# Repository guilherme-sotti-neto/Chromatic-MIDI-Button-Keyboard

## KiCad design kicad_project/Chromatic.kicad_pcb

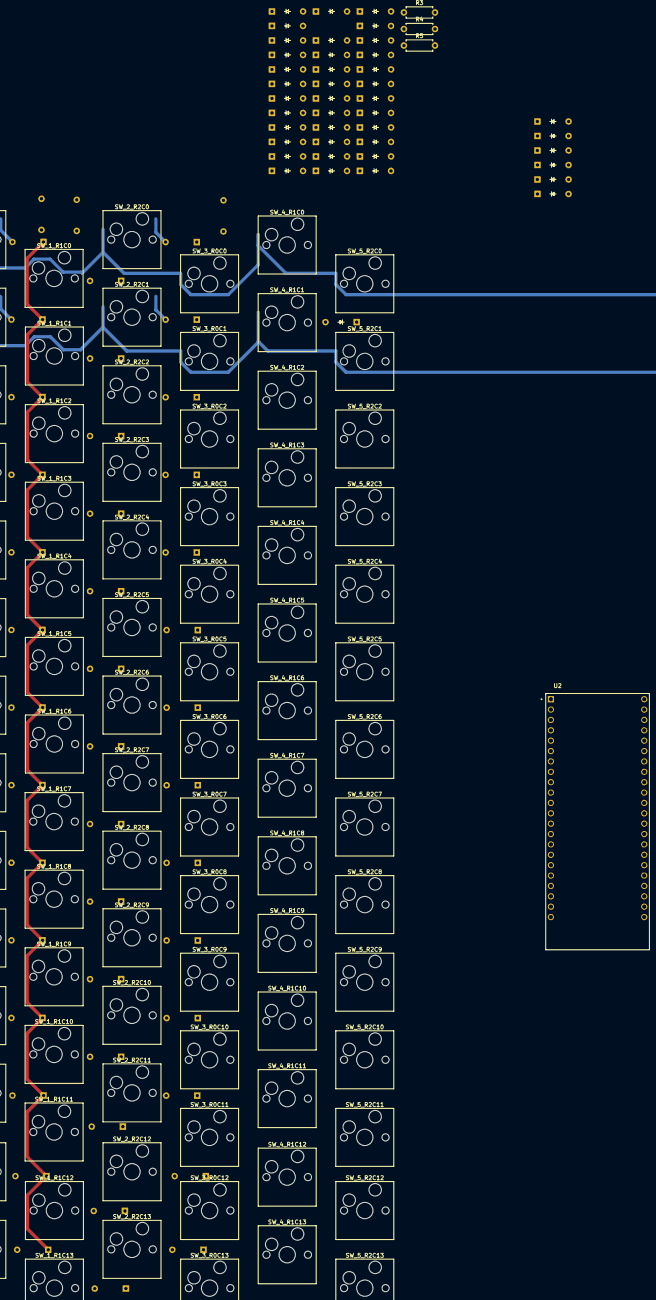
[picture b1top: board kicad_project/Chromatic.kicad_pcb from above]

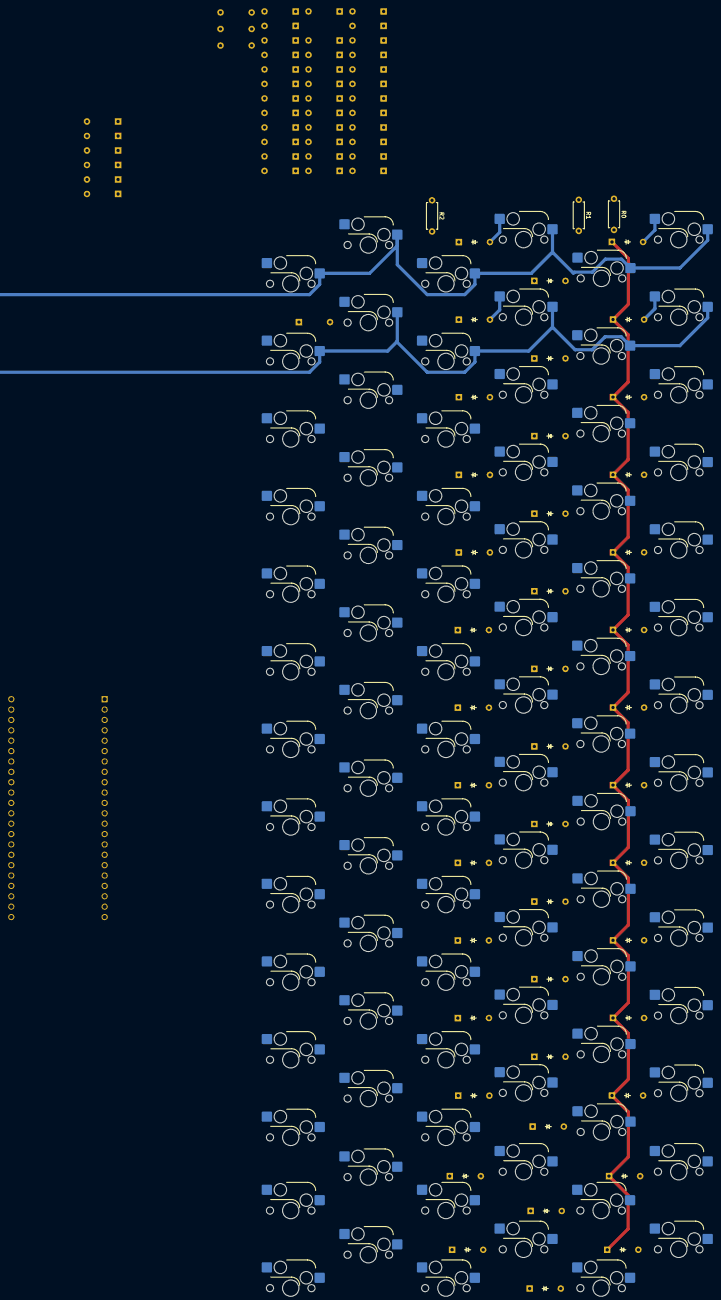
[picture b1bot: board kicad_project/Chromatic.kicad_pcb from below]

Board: 2 copper layers, 175 parts (45 on the bottom side), 108 nets.

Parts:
D_R0C0, D_R0C1, D_R0C2, D_R0C3, D_R0C4, D_R0C5, D_R0C6, D_R0C7, D_R0C8, D_R0C9, D_R0C10, D_R0C11, D_R0C12, D_R0C13, D_R1C0, D_R1C1, D_R1C2, D_R1C3, D_R1C4, D_R1C5, D_R1C6, D_R1C7, D_R1C8, D_R1C9, D_R1C10, D_R1C11, D_R1C12, D_R1C13, D_R2C0, D_R2C1, D_R2C2, D_R2C3, D_R2C4, D_R2C5, D_R2C6, D_R2C7, D_R2C8, D_R2C9, D_R2C10, D_R2C11, D_R2C12, D_R2C13, D_R2C17, D_R2C18, D_R2C19, D_R2C20, D_R2C21, D_R2C22, D_R2C23, D_R2C24, D_R2C25, D_R2C26, D_R2C27, D_R2C28, D_R2C29, D_R2C30, D_R2C31, D_R2C32, D_R2C33, D_R2C34, D_R2C35, D_R2C36, D_R2C37, D_R2C38, D_R2C39, D_R2C40, D_R2C41, D_R2C42, D_R2C43, D_R2C44, D_R2C45, D_R2C46, D_R2C47, D_R2C48, D_R2C49, D_R2C50, D_R2C51, D_R2C52, D_R2C53, D_R2C54, D_R2C55, D_R2C56, D_R2C57, D_R2C58: Diode_DO-35
R0, R1, R2, R3, R4, R5: Resistor; R_Axial_DIN0207_L6.3mm_D2.5mm_P7.62mm_Horizontal
SW_0_R0C0, SW_0_R0C1, SW_0_R0C2, SW_0_R0C3, SW_0_R0C4, SW_0_R0C5, SW_0_R0C6, SW_0_R0C7, SW_0_R0C8, SW_0_R0C9, SW_0_R0C10, SW_0_R0C11, SW_0_R0C12, SW_0_R0C13, SW_1_R1C0, SW_1_R1C1, SW_1_R1C2, SW_1_R1C3, SW_1_R1C4, SW_1_R1C5, SW_1_R1C6, SW_1_R1C7, SW_1_R1C8, SW_1_R1C9, SW_1_R1C10, SW_1_R1C11, SW_1_R1C12, SW_1_R1C13, SW_2_R2C0, SW_2_R2C1, SW_2_R2C2, SW_2_R2C3, SW_2_R2C4, SW_2_R2C5, SW_2_R2C6, SW_2_R2C7, SW_2_R2C8, SW_2_R2C9, SW_2_R2C10, SW_2_R2C11, SW_2_R2C12, SW_2_R2C13, SW_3_R0C0, SW_3_R0C1, SW_3_R0C2, SW_3_R0C3, SW_3_R0C4, SW_3_R0C5, SW_3_R0C6, SW_3_R0C7, SW_3_R0C8, SW_3_R0C9, SW_3_R0C10, SW_3_R0C11, SW_3_R0C12, SW_3_R0C13, SW_4_R1C0, SW_4_R1C1, SW_4_R1C2, SW_4_R1C3, SW_4_R1C4, SW_4_R1C5, SW_4_R1C6, SW_4_R1C7, SW_4_R1C8, SW_4_R1C9, SW_4_R1C10, SW_4_R1C11, SW_4_R1C12, SW_4_R1C13, SW_5_R2C0, SW_5_R2C1, SW_5_R2C2, SW_5_R2C3, SW_5_R2C4, SW_5_R2C5, SW_5_R2C6, SW_5_R2C7, SW_5_R2C8, SW_5_R2C9, SW_5_R2C10, SW_5_R2C11, SW_5_R2C12, SW_5_R2C13: Keyswitch; Hotswap_MX_1.00u
U2: ESP32-S3-DEVKITC-1-N8R8

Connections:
Column 0: SW_0_R0C0.1, SW_1_R1C0.1, SW_2_R2C0.1, SW_3_R0C0.1, SW_4_R1C0.1, SW_5_R2C0.1, U2.J1_4 (GPIO4)
Column 1: SW_0_R0C1.1, SW_1_R1C1.1, SW_2_R2C1.1, SW_3_R0C1.1, SW_4_R1C1.1, SW_5_R2C1.1, U2.J1_5 (GPIO5)
Column 2: SW_0_R0C2.1, SW_1_R1C2.1, SW_2_R2C2.1, SW_3_R0C2.1, SW_4_R1C2.1, SW_5_R2C2.1, U2.J1_6 (GPIO6)
Column 3: SW_0_R0C3.1, SW_1_R1C3.1, SW_2_R2C3.1, SW_3_R0C3.1, SW_4_R1C3.1, SW_5_R2C3.1, U2.J1_7 (GPIO7)
Column 4: SW_0_R0C4.1, SW_1_R1C4.1, SW_2_R2C4.1, SW_3_R0C4.1, SW_4_R1C4.1, SW_5_R2C4.1, U2.J1_8 (GPIO15)
Column 5: SW_0_R0C5.1, SW_1_R1C5.1, SW_2_R2C5.1, SW_3_R0C5.1, SW_4_R1C5.1, SW_5_R2C5.1, U2.J1_9 (GPIO16)
Column 6: SW_0_R0C6.1, SW_1_R1C6.1, SW_2_R2C6.1, SW_3_R0C6.1, SW_4_R1C6.1, SW_5_R2C6.1, U2.J1_10 (GPIO17)
Column 7: SW_0_R0C7.1, SW_1_R1C7.1, SW_2_R2C7.1, SW_3_R0C7.1, SW_4_R1C7.1, SW_5_R2C7.1, U2.J1_11 (GPIO18)
Column 8: SW_0_R0C8.1, SW_1_R1C8.1, SW_2_R2C8.1, SW_3_R0C8.1, SW_4_R1C8.1, SW_5_R2C8.1, U2.J1_12 (GPIO8)
Column 9: SW_0_R0C9.1, SW_0_R0C12.1, SW_1_R1C9.1, SW_1_R1C12.1, SW_2_R2C9.1, SW_2_R2C12.1, SW_3_R0C9.1, SW_3_R0C12.1, SW_4_R1C9.1, SW_4_R1C12.1, SW_5_R2C9.1, SW_5_R2C12.1, U2.J1_13 (GPIO3)
Column 10: SW_0_R0C10.1, SW_0_R0C13.1, SW_1_R1C10.1, SW_1_R1C13.1, SW_2_R2C10.1, SW_2_R2C13.1, SW_3_R0C10.1, SW_3_R0C13.1, SW_4_R1C10.1, SW_4_R1C13.1, SW_5_R2C10.1, SW_5_R2C13.1, U2.J1_14 (GPIO46)
Column 11: SW_0_R0C11.1, SW_1_R1C11.1, SW_2_R2C11.1, SW_3_R0C11.1, SW_4_R1C11.1, SW_5_R2C11.1, U2.J1_15 (GPIO9)
unnamed: D_R0C0.2 (A), SW_0_R0C0.2
unnamed: D_R0C0.1 (K), D_R0C1.1 (K), D_R0C2.1 (K), D_R0C3.1 (K), D_R0C4.1 (K), D_R0C5.1 (K), D_R0C6.1 (K), D_R0C7.1 (K), D_R0C8.1 (K), D_R0C9.1 (K), D_R0C10.1 (K), D_R0C11.1 (K), D_R0C12.1 (K), D_R0C13.1 (K), R0.2
unnamed: D_R0C1.2 (A), SW_0_R0C1.2
unnamed: D_R0C2.2 (A), SW_0_R0C2.2
unnamed: D_R0C3.2 (A), SW_0_R0C3.2
unnamed: D_R0C4.2 (A), SW_0_R0C4.2
unnamed: D_R0C5.2 (A), SW_0_R0C5.2
unnamed: D_R0C6.2 (A), SW_0_R0C6.2
unnamed: D_R0C7.2 (A), SW_0_R0C7.2
unnamed: D_R0C8.2 (A), SW_0_R0C8.2
unnamed: D_R0C9.2 (A), SW_0_R0C9.2
unnamed: D_R0C10.2 (A), SW_0_R0C10.2
unnamed: D_R0C11.2 (A), SW_0_R0C11.2
unnamed: D_R0C12.2 (A), SW_0_R0C12.2
unnamed: D_R0C13.2 (A), SW_0_R0C13.2
unnamed: D_R1C0.2 (A), SW_1_R1C0.2
unnamed: D_R1C0.1 (K), D_R1C1.1 (K), D_R1C2.1 (K), D_R1C3.1 (K), D_R1C4.1 (K), D_R1C5.1 (K), D_R1C6.1 (K), D_R1C7.1 (K), D_R1C8.1 (K), D_R1C9.1 (K), D_R1C10.1 (K), D_R1C11.1 (K), D_R1C12.1 (K), D_R1C13.1 (K), R1.2
unnamed: D_R1C1.2 (A), SW_1_R1C1.2
unnamed: D_R1C2.2 (A), SW_1_R1C2.2
unnamed: D_R1C3.2 (A), SW_1_R1C3.2
unnamed: D_R1C4.2 (A), SW_1_R1C4.2
unnamed: D_R1C5.2 (A), SW_1_R1C5.2
unnamed: D_R1C6.2 (A), SW_1_R1C6.2
unnamed: D_R1C7.2 (A), SW_1_R1C7.2
unnamed: D_R1C8.2 (A), SW_1_R1C8.2
unnamed: D_R1C9.2 (A), SW_1_R1C9.2
unnamed: D_R1C10.2 (A), SW_1_R1C10.2
unnamed: D_R1C11.2 (A), SW_1_R1C11.2
unnamed: D_R1C12.2 (A), SW_1_R1C12.2
unnamed: D_R1C13.2 (A), SW_1_R1C13.2
unnamed: D_R2C0.2 (A), SW_2_R2C0.2
unnamed: D_R2C0.1 (K), D_R2C1.1 (K), D_R2C2.1 (K), D_R2C3.1 (K), D_R2C4.1 (K), D_R2C5.1 (K), D_R2C6.1 (K), D_R2C7.1 (K), D_R2C8.1 (K), D_R2C9.1 (K), D_R2C10.1 (K), D_R2C11.1 (K), D_R2C12.1 (K), D_R2C13.1 (K), R2.2
unnamed: D_R2C1.2 (A), SW_2_R2C1.2
unnamed: D_R2C2.2 (A), SW_2_R2C2.2
unnamed: D_R2C3.2 (A), SW_2_R2C3.2
unnamed: D_R2C4.2 (A), SW_2_R2C4.2
unnamed: D_R2C5.2 (A), SW_2_R2C5.2
unnamed: D_R2C6.2 (A), SW_2_R2C6.2
unnamed: D_R2C7.2 (A), SW_2_R2C7.2
unnamed: D_R2C8.2 (A), SW_2_R2C8.2
unnamed: D_R2C9.2 (A), SW_2_R2C9.2
unnamed: D_R2C10.2 (A), SW_2_R2C10.2
unnamed: D_R2C11.2 (A), SW_2_R2C11.2
unnamed: D_R2C12.2 (A), SW_2_R2C12.2
unnamed: D_R2C13.2 (A), SW_2_R2C13.2
unnamed: D_R2C17.2 (A), SW_5_R2C0.2
unnamed: D_R2C17.1 (K), D_R2C18.1 (K), D_R2C19.1 (K), D_R2C20.1 (K), D_R2C21.1 (K), D_R2C22.1 (K), D_R2C23.1 (K), D_R2C24.1 (K), D_R2C25.1 (K), D_R2C26.1 (K), D_R2C27.1 (K), D_R2C28.1 (K), D_R2C55.1 (K), D_R2C58.1 (K), R3.2
unnamed: D_R2C18.2 (A), SW_5_R2C1.2
unnamed: D_R2C19.2 (A), SW_5_R2C2.2
unnamed: D_R2C20.2 (A), SW_5_R2C3.2
unnamed: D_R2C21.2 (A), SW_5_R2C4.2
unnamed: D_R2C22.2 (A), SW_5_R2C5.2
unnamed: D_R2C23.2 (A), SW_5_R2C6.2
unnamed: D_R2C24.2 (A), SW_5_R2C7.2
unnamed: D_R2C25.2 (A), SW_5_R2C8.2
unnamed: D_R2C26.2 (A), SW_5_R2C9.2
unnamed: D_R2C27.2 (A), SW_5_R2C10.2
unnamed: D_R2C28.2 (A), SW_5_R2C11.2
unnamed: D_R2C29.2 (A), SW_4_R1C0.2
unnamed: D_R2C29.1 (K), D_R2C30.1 (K), D_R2C31.1 (K), D_R2C32.1 (K), D_R2C33.1 (K), D_R2C34.1 (K), D_R2C35.1 (K), D_R2C36.1 (K), D_R2C37.1 (K), D_R2C38.1 (K), D_R2C39.1 (K), D_R2C40.1 (K), D_R2C54.1 (K), D_R2C57.1 (K), R4.2
unnamed: D_R2C30.2 (A), SW_4_R1C1.2
unnamed: D_R2C31.2 (A), SW_4_R1C2.2
unnamed: D_R2C32.2 (A), SW_4_R1C3.2
unnamed: D_R2C33.2 (A), SW_4_R1C4.2
unnamed: D_R2C34.2 (A), SW_4_R1C5.2
unnamed: D_R2C35.2 (A), SW_4_R1C6.2
unnamed: D_R2C36.2 (A), SW_4_R1C7.2
unnamed: D_R2C37.2 (A), SW_4_R1C8.2
unnamed: D_R2C38.2 (A), SW_4_R1C9.2
unnamed: D_R2C39.2 (A), SW_4_R1C10.2
unnamed: D_R2C40.2 (A), SW_4_R1C11.2
unnamed: D_R2C41.2 (A), SW_3_R0C0.2
unnamed: D_R2C41.1 (K), D_R2C42.1 (K), D_R2C43.1 (K), D_R2C44.1 (K), D_R2C45.1 (K), D_R2C46.1 (K), D_R2C47.1 (K), D_R2C48.1 (K), D_R2C49.1 (K), D_R2C50.1 (K), D_R2C51.1 (K), D_R2C52.1 (K), D_R2C53.1 (K), D_R2C56.1 (K), R5.2
unnamed: D_R2C42.2 (A), SW_3_R0C1.2
unnamed: D_R2C43.2 (A), SW_3_R0C2.2
unnamed: D_R2C44.2 (A), SW_3_R0C3.2
unnamed: D_R2C45.2 (A), SW_3_R0C4.2
unnamed: D_R2C46.2 (A), SW_3_R0C5.2
unnamed: D_R2C47.2 (A), SW_3_R0C6.2
unnamed: D_R2C48.2 (A), SW_3_R0C7.2
unnamed: D_R2C49.2 (A), SW_3_R0C8.2
unnamed: D_R2C50.2 (A), SW_3_R0C9.2
unnamed: D_R2C51.2 (A), SW_3_R0C10.2
unnamed: D_R2C52.2 (A), SW_3_R0C11.2
unnamed: D_R2C53.2 (A), SW_3_R0C12.2
unnamed: D_R2C54.2 (A), SW_4_R1C12.2
unnamed: D_R2C55.2 (A), SW_5_R2C12.2
unnamed: D_R2C56.2 (A), SW_3_R0C13.2
unnamed: D_R2C57.2 (A), SW_4_R1C13.2
unnamed: D_R2C58.2 (A), SW_5_R2C13.2
Row 0: R0.1, U2.J3_3 (U0RXD/GPIO44)
Row 1: R5.1, U2.J3_4 (GPIO1)
Row 2: R1.1, U2.J3_5 (GPIO2)
Row 3: R4.1, U2.J3_16 (GPIO48)
Row 4: R2.1, U2.J3_17 (GPIO47)
Row 5: R3.1, U2.J3_18 (GPIO21)

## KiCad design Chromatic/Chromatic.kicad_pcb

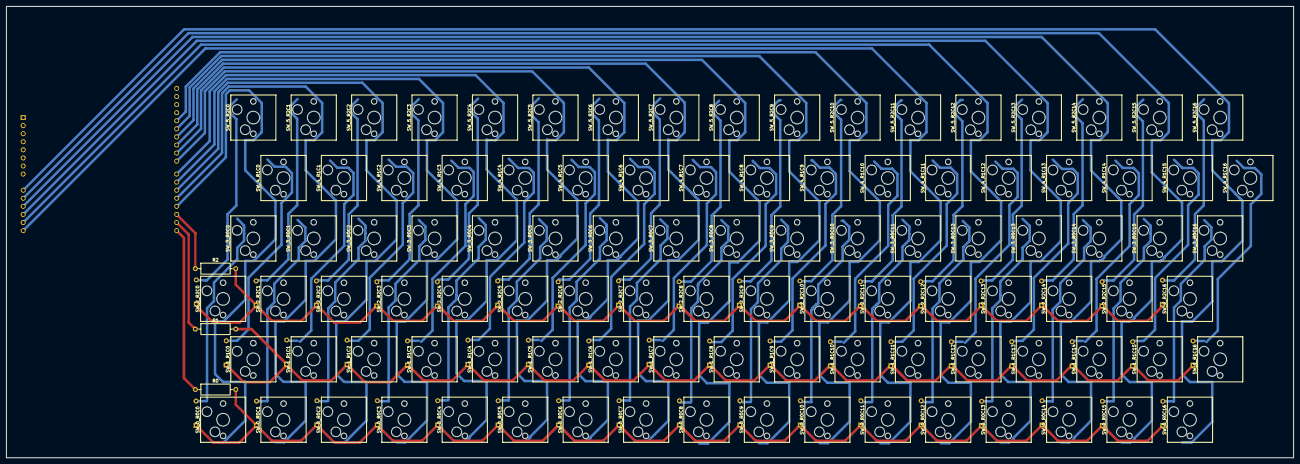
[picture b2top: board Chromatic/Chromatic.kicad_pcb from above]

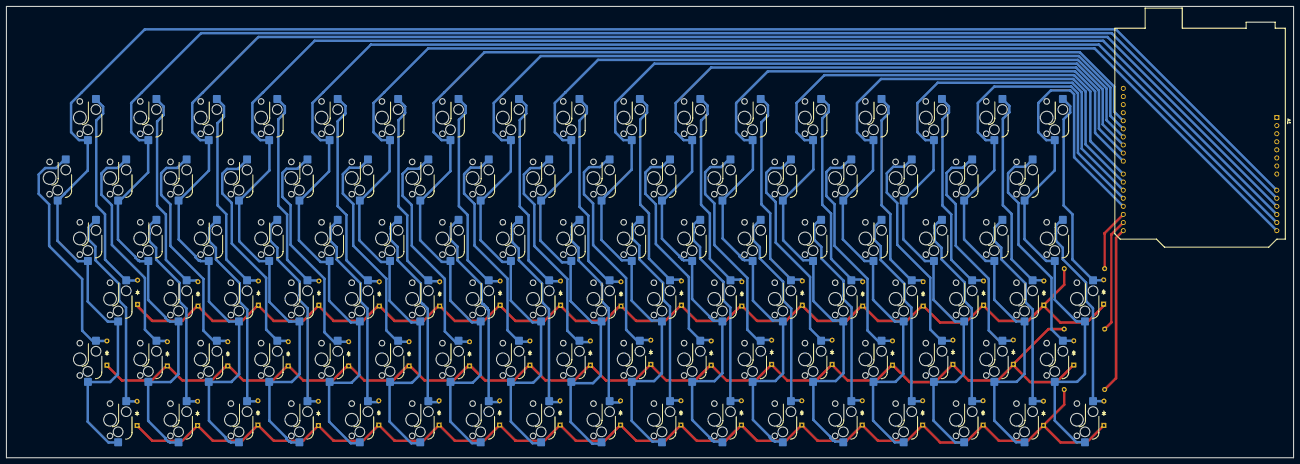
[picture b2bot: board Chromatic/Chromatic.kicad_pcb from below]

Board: 2 copper layers, 404.7 x 141.9 mm, 157 parts (52 on the bottom side), 74 nets.

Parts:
A1: Arduino_Leonardo; Arduino_UNO_R3
D_R0C0, D_R0C1, D_R0C2, D_R0C3, D_R0C4, D_R0C5, D_R0C6, D_R0C7, D_R0C8, D_R0C9, D_R0C10, D_R0C11, D_R0C12, D_R0C13, D_R0C14, D_R0C15, D_R0C16, D_R1C0, D_R1C1, D_R1C2, D_R1C3, D_R1C4, D_R1C5, D_R1C6, D_R1C7, D_R1C8, D_R1C9, D_R1C10, D_R1C11, D_R1C12, D_R1C13, D_R1C14, D_R1C15, D_R1C16, D_R2C0, D_R2C1, D_R2C2, D_R2C3, D_R2C4, D_R2C5, D_R2C6, D_R2C7, D_R2C8, D_R2C9, D_R2C10, D_R2C11, D_R2C12, D_R2C13, D_R2C14, D_R2C15, D_R2C16: Diode_DO-35
R0, R1, R2: Resistor; R_Axial_DIN0309_L9.0mm_D3.2mm_P12.70mm_Horizontal
SW_0_R0C0, SW_0_R0C1, SW_0_R0C2, SW_0_R0C3, SW_0_R0C4, SW_0_R0C5, SW_0_R0C6, SW_0_R0C7, SW_0_R0C8, SW_0_R0C9, SW_0_R0C10, SW_0_R0C11, SW_0_R0C12, SW_0_R0C13, SW_0_R0C14, SW_0_R0C15, SW_0_R0C16, SW_1_R1C0, SW_1_R1C1, SW_1_R1C2, SW_1_R1C3, SW_1_R1C4, SW_1_R1C5, SW_1_R1C6, SW_1_R1C7, SW_1_R1C8, SW_1_R1C9, SW_1_R1C10, SW_1_R1C11, SW_1_R1C12, SW_1_R1C13, SW_1_R1C14, SW_1_R1C15, SW_1_R1C16, SW_2_R2C0, SW_2_R2C1, SW_2_R2C2, SW_2_R2C3, SW_2_R2C4, SW_2_R2C5, SW_2_R2C6, SW_2_R2C7, SW_2_R2C8, SW_2_R2C9, SW_2_R2C10, SW_2_R2C11, SW_2_R2C12, SW_2_R2C13, SW_2_R2C14, SW_2_R2C15, SW_2_R2C16, SW_3_R0C0, SW_3_R0C1, SW_3_R0C2, SW_3_R0C3, SW_3_R0C4, SW_3_R0C5, SW_3_R0C6, SW_3_R0C7, SW_3_R0C8, SW_3_R0C9, SW_3_R0C10, SW_3_R0C11, SW_3_R0C12, SW_3_R0C13, SW_3_R0C14, SW_3_R0C15, SW_3_R0C16, SW_4_R1C0, SW_4_R1C1, SW_4_R1C2, SW_4_R1C3, SW_4_R1C4, SW_4_R1C5, SW_4_R1C6, SW_4_R1C7, SW_4_R1C8, SW_4_R1C9, SW_4_R1C10, SW_4_R1C11, SW_4_R1C12, SW_4_R1C13, SW_4_R1C14, SW_4_R1C15, SW_4_R1C16, SW_5_R2C0, SW_5_R2C1, SW_5_R2C2, SW_5_R2C3, SW_5_R2C4, SW_5_R2C5, SW_5_R2C6, SW_5_R2C7, SW_5_R2C8, SW_5_R2C9, SW_5_R2C10, SW_5_R2C11, SW_5_R2C12, SW_5_R2C13, SW_5_R2C14, SW_5_R2C15, SW_5_R2C16: Keyswitch; Hotswap_MX_1.00u

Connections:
Column 0: A1.18 (D3/SCL), SW_0_R0C0.1, SW_1_R1C0.1, SW_2_R2C0.1, SW_3_R0C0.1, SW_4_R1C0.1, SW_5_R2C0.1
Column 1: A1.19 (D4), SW_0_R0C1.1, SW_1_R1C1.1, SW_2_R2C1.1, SW_3_R0C1.1, SW_4_R1C1.1, SW_5_R2C1.1
Column 2: A1.20 (D5), SW_0_R0C2.1, SW_1_R1C2.1, SW_2_R2C2.1, SW_3_R0C2.1, SW_4_R1C2.1, SW_5_R2C2.1
Column 3: A1.21 (D6), SW_0_R0C3.1, SW_1_R1C3.1, SW_2_R2C3.1, SW_3_R0C3.1, SW_4_R1C3.1, SW_5_R2C3.1
Column 4: A1.22 (D7), SW_0_R0C4.1, SW_1_R1C4.1, SW_2_R2C4.1, SW_3_R0C4.1, SW_4_R1C4.1, SW_5_R2C4.1
Column 5: A1.23 (D8), SW_0_R0C5.1, SW_1_R1C5.1, SW_2_R2C5.1, SW_3_R0C5.1, SW_4_R1C5.1, SW_5_R2C5.1
Column 6: A1.24 (D9), SW_0_R0C6.1, SW_1_R1C6.1, SW_2_R2C6.1, SW_3_R0C6.1, SW_4_R1C6.1, SW_5_R2C6.1
Column 7: A1.25 (D10), SW_0_R0C7.1, SW_1_R1C7.1, SW_2_R2C7.1, SW_3_R0C7.1, SW_4_R1C7.1, SW_5_R2C7.1
Column 8: A1.26 (D11), SW_0_R0C8.1, SW_1_R1C8.1, SW_2_R2C8.1, SW_3_R0C8.1, SW_4_R1C8.1, SW_5_R2C8.1
Column 9: A1.27 (D12), SW_0_R0C9.1, SW_1_R1C9.1, SW_2_R2C9.1, SW_3_R0C9.1, SW_4_R1C9.1, SW_5_R2C9.1
Column 10: A1.28 (D13), SW_0_R0C10.1, SW_1_R1C10.1, SW_2_R2C10.1, SW_3_R0C10.1, SW_4_R1C10.1, SW_5_R2C10.1
Column 11: A1.14 (A5), SW_0_R0C11.1, SW_1_R1C11.1, SW_2_R2C11.1, SW_3_R0C11.1, SW_4_R1C11.1, SW_5_R2C11.1
Column 12: A1.13 (A4), SW_0_R0C12.1, SW_1_R1C12.1, SW_2_R2C12.1, SW_3_R0C12.1, SW_4_R1C12.1, SW_5_R2C12.1
Column 13: A1.12 (A3), SW_0_R0C13.1, SW_1_R1C13.1, SW_2_R2C13.1, SW_3_R0C13.1, SW_4_R1C13.1, SW_5_R2C13.1
Column 14: A1.11 (A2), SW_0_R0C14.1, SW_1_R1C14.1, SW_2_R2C14.1, SW_3_R0C14.1, SW_4_R1C14.1, SW_5_R2C14.1
Column 15: A1.10 (A1), SW_0_R0C15.1, SW_1_R1C15.1, SW_2_R2C15.1, SW_3_R0C15.1, SW_4_R1C15.1, SW_5_R2C15.1
Column 16: A1.9 (A0), SW_0_R0C16.1, SW_1_R1C16.1, SW_2_R2C16.1, SW_3_R0C16.1, SW_4_R1C16.1, SW_5_R2C16.1
unnamed: D_R0C0.2 (A), SW_0_R0C0.2, SW_3_R0C0.2
unnamed: D_R0C0.1 (K), D_R0C1.1 (K), D_R0C2.1 (K), D_R0C3.1 (K), D_R0C4.1 (K), D_R0C5.1 (K), D_R0C6.1 (K), D_R0C7.1 (K), D_R0C8.1 (K), D_R0C9.1 (K), D_R0C10.1 (K), D_R0C11.1 (K), D_R0C12.1 (K), D_R0C13.1 (K), D_R0C14.1 (K), D_R0C15.1 (K), D_R0C16.1 (K), R0.2
unnamed: D_R0C1.2 (A), SW_0_R0C1.2, SW_3_R0C1.2
unnamed: D_R0C2.2 (A), SW_0_R0C2.2, SW_3_R0C2.2
unnamed: D_R0C3.2 (A), SW_0_R0C3.2, SW_3_R0C3.2
unnamed: D_R0C4.2 (A), SW_0_R0C4.2, SW_3_R0C4.2
unnamed: D_R0C5.2 (A), SW_0_R0C5.2, SW_3_R0C5.2
unnamed: D_R0C6.2 (A), SW_0_R0C6.2, SW_3_R0C6.2
unnamed: D_R0C7.2 (A), SW_0_R0C7.2, SW_3_R0C7.2
unnamed: D_R0C8.2 (A), SW_0_R0C8.2, SW_3_R0C8.2
unnamed: D_R0C9.2 (A), SW_0_R0C9.2, SW_3_R0C9.2
unnamed: D_R0C10.2 (A), SW_0_R0C10.2, SW_3_R0C10.2
unnamed: D_R0C11.2 (A), SW_0_R0C11.2, SW_3_R0C11.2
unnamed: D_R0C12.2 (A), SW_0_R0C12.2, SW_3_R0C12.2
unnamed: D_R0C13.2 (A), SW_0_R0C13.2, SW_3_R0C13.2
unnamed: D_R0C14.2 (A), SW_0_R0C14.2, SW_3_R0C14.2
unnamed: D_R0C15.2 (A), SW_0_R0C15.2, SW_3_R0C15.2
unnamed: D_R0C16.2 (A), SW_0_R0C16.2, SW_3_R0C16.2
unnamed: D_R1C0.2 (A), SW_1_R1C0.2, SW_4_R1C0.2
unnamed: D_R1C0.1 (K), D_R1C1.1 (K), D_R1C2.1 (K), D_R1C3.1 (K), D_R1C4.1 (K), D_R1C5.1 (K), D_R1C6.1 (K), D_R1C7.1 (K), D_R1C8.1 (K), D_R1C9.1 (K), D_R1C10.1 (K), D_R1C11.1 (K), D_R1C12.1 (K), D_R1C13.1 (K), D_R1C14.1 (K), D_R1C15.1 (K), D_R1C16.1 (K), R1.2
unnamed: D_R1C1.2 (A), SW_1_R1C1.2, SW_4_R1C1.2
unnamed: D_R1C2.2 (A), SW_1_R1C2.2, SW_4_R1C2.2
unnamed: D_R1C3.2 (A), SW_1_R1C3.2, SW_4_R1C3.2
unnamed: D_R1C4.2 (A), SW_1_R1C4.2, SW_4_R1C4.2
unnamed: D_R1C5.2 (A), SW_1_R1C5.2, SW_4_R1C5.2
unnamed: D_R1C6.2 (A), SW_1_R1C6.2, SW_4_R1C6.2
unnamed: D_R1C7.2 (A), SW_1_R1C7.2, SW_4_R1C7.2
unnamed: D_R1C8.2 (A), SW_1_R1C8.2, SW_4_R1C8.2
unnamed: D_R1C9.2 (A), SW_1_R1C9.2, SW_4_R1C9.2
unnamed: D_R1C10.2 (A), SW_1_R1C10.2, SW_4_R1C10.2
unnamed: D_R1C11.2 (A), SW_1_R1C11.2, SW_4_R1C11.2
unnamed: D_R1C12.2 (A), SW_1_R1C12.2, SW_4_R1C12.2
unnamed: D_R1C13.2 (A), SW_1_R1C13.2, SW_4_R1C13.2
unnamed: D_R1C14.2 (A), SW_1_R1C14.2, SW_4_R1C14.2
unnamed: D_R1C15.2 (A), SW_1_R1C15.2, SW_4_R1C15.2
unnamed: D_R1C16.2 (A), SW_1_R1C16.2, SW_4_R1C16.2
unnamed: D_R2C0.2 (A), SW_2_R2C0.2, SW_5_R2C0.2
unnamed: D_R2C0.1 (K), D_R2C1.1 (K), D_R2C2.1 (K), D_R2C3.1 (K), D_R2C4.1 (K), D_R2C5.1 (K), D_R2C6.1 (K), D_R2C7.1 (K), D_R2C8.1 (K), D_R2C9.1 (K), D_R2C10.1 (K), D_R2C11.1 (K), D_R2C12.1 (K), D_R2C13.1 (K), D_R2C14.1 (K), D_R2C15.1 (K), D_R2C16.1 (K), R2.2
unnamed: D_R2C1.2 (A), SW_2_R2C1.2, SW_5_R2C1.2
unnamed: D_R2C2.2 (A), SW_2_R2C2.2, SW_5_R2C2.2
unnamed: D_R2C3.2 (A), SW_2_R2C3.2, SW_5_R2C3.2
unnamed: D_R2C4.2 (A), SW_2_R2C4.2, SW_5_R2C4.2
unnamed: D_R2C5.2 (A), SW_2_R2C5.2, SW_5_R2C5.2
unnamed: D_R2C6.2 (A), SW_2_R2C6.2, SW_5_R2C6.2
unnamed: D_R2C7.2 (A), SW_2_R2C7.2, SW_5_R2C7.2
unnamed: D_R2C8.2 (A), SW_2_R2C8.2, SW_5_R2C8.2
unnamed: D_R2C9.2 (A), SW_2_R2C9.2, SW_5_R2C9.2
unnamed: D_R2C10.2 (A), SW_2_R2C10.2, SW_5_R2C10.2
unnamed: D_R2C11.2 (A), SW_2_R2C11.2, SW_5_R2C11.2
unnamed: D_R2C12.2 (A), SW_2_R2C12.2, SW_5_R2C12.2
unnamed: D_R2C13.2 (A), SW_2_R2C13.2, SW_5_R2C13.2
unnamed: D_R2C14.2 (A), SW_2_R2C14.2, SW_5_R2C14.2
unnamed: D_R2C15.2 (A), SW_2_R2C15.2, SW_5_R2C15.2
unnamed: D_R2C16.2 (A), SW_2_R2C16.2, SW_5_R2C16.2
Row 0: A1.15 (D0/RX), R0.1
Row 1: A1.16 (D1/TX), R1.1
Row 2: A1.17 (D2/SDA), R2.1

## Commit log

2026-04-20 Create LICENSE
2026-04-20 Rename LICENSE to LICENSE.md
2026-04-22 octave adjust
2026-04-22 atualização
2026-04-22 removido files
2026-04-22 nomes
2026-04-22 atualização de comentários
2026-04-23 pc utf
2026-04-23 arrumadas as bibliotecas
2026-04-24 separados grupos
2026-04-25 layout
2026-04-26 groups
2026-04-26 COPPER LAYERS
2026-04-26 CONNECTIONS FIXED
2026-04-27 convertido pra versão 9.0 kicad
2026-04-27 kicad rpm version
2026-06-26 TROCADO ARDUINO POR ESP
2026-06-30 arrumado pcb e footprint
